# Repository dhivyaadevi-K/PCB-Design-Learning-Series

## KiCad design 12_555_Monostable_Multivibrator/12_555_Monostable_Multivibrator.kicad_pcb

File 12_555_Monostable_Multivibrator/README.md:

# 12 - NE555 Monostable Push-Button Timer

A beginner-friendly PCB project designed in KiCad 9 to practice building a 555 timer monostable ("one-shot") circuit, where pressing a push button lights an LED for a fixed duration.

Part of my **PCB Design Learning Series**, where I design and document circuits from basic to advanced using KiCad.

## Software Used

Designed in **KiCad 9**

## Overview

U1 (NE555P) is configured in monostable mode. Pressing SW1 momentarily pulls the TRIGGER pin (pin 2) low, starting a single timing cycle. During this cycle, the output (pin 3) goes high, lighting LED D1 through current-limiting resistor R3. After the timing period set by R2 and C1 elapses, the output returns low and the LED turns off — until the button is pressed again.

| J1 Pin | Signal | Description        |
|--------|--------|---------------------|
| 1      | +5V    | Power input          |
| 2      | GND    | Common ground        |

## How It Works

- R1 (10k) pulls the TRIGGER pin (pin 2) high when SW1 is not pressed, keeping the timer idle
- Pressing SW1 momentarily connects TRIGGER to GND, dropping it below 1/3 VCC and starting the timing cycle
- Once triggered, the output (pin 3, Q) goes high regardless of further trigger changes, lighting D1 through R3 (330 Ω)
- R2 (100k) and C1 (10 µF) set the output pulse duration, charging until the THRESHOLD pin (pin 6) reaches 2/3 VCC, at which point the output resets low and D1 turns off
- C2 (10n) on the CV pin (pin 5) stabilizes the internal reference voltage against noise
- Approximate pulse duration: **t ≈ 1.1 × R2 × C1**

## Features

- Through-hole PCB, beginner-friendly assembly
- Push-button triggered NE555 monostable (one-shot) timer
- LED lights for a fixed, predictable duration per button press
- Noise-stabilizing control voltage capacitor
- ERC and DRC verified
- Gerber and drill files included, ready for fabrication

## Components

| Component             | Qty |
|--------------------------|-----|
| NE555P Timer IC (U1)     | 1   |
| Push Button (SW1)        | 1   |
| LED (D1)                 | 1   |
| 330 Ω Resistor (R3)      | 1   |
| 10k Resistor (R1)        | 1   |
| 100k Resistor (R2)       | 1   |
| 10 µF Capacitor (C1)     | 1   |
| 10n Capacitor (C2)       | 1   |
| 2-Pin Header (J1)        | 1   |

## Repository Contents

- KiCad Schematic
- KiCad PCB
- Gerber Files
- Drill Files
- ERC Report
- DRC Report
- Images

## Images

### Schematic

### PCB Layout

### 3D View

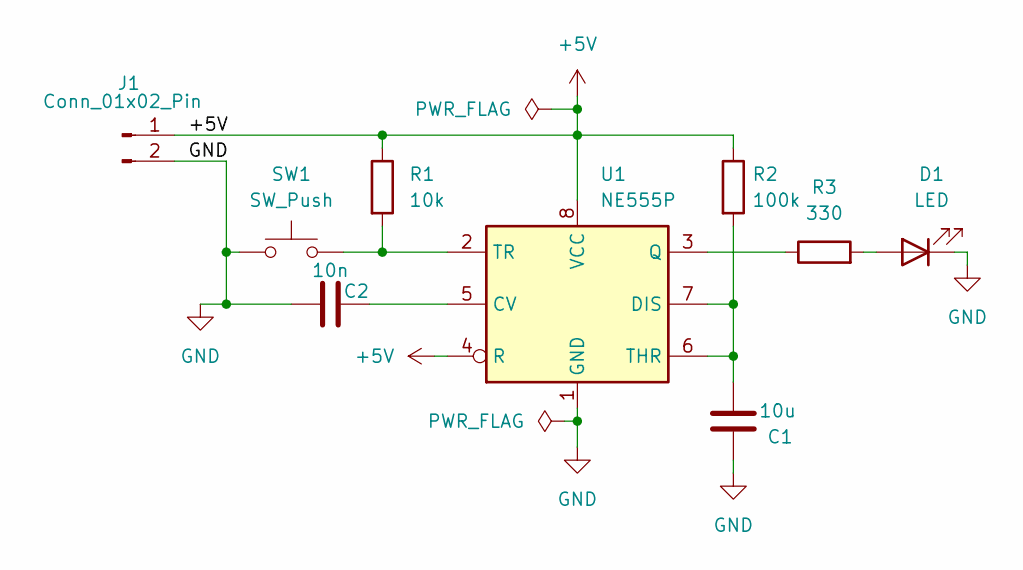
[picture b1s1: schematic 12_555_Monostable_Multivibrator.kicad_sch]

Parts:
C1: 10u; C_Disc_D5.0mm_W2.5mm_P5.00mm
C2: 10n; C_Disc_D5.0mm_W2.5mm_P5.00mm
D1: LED; LED_D5.0mm
J1: Conn_01x02_Pin; PinHeader_1x02_P2.54mm_Vertical
R1: 10k; R_Axial_DIN0207_L6.3mm_D2.5mm_P7.62mm_Horizontal
R2: 100k; R_Axial_DIN0207_L6.3mm_D2.5mm_P7.62mm_Horizontal
R3: 330; R_Axial_DIN0207_L6.3mm_D2.5mm_P7.62mm_Horizontal
SW1: SW_Push; SW_PUSH_6mm_H5mm
U1: NE555P; DIP-8_W7.62mm

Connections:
+5V: J1.1, R1.1, R2.1, U1.4 (R), U1.8 (VCC)
GND: C1.2, C2.1, D1.1 (K), J1.2, SW1.1, U1.1 (GND)
unnamed: D1.2 (A), R3.2
unnamed: C2.2, U1.5 (CV)
unnamed: C1.1, R2.2, U1.6 (THR), U1.7 (DIS)
unnamed: R3.1, U1.3 (Q)
unnamed: R1.2, SW1.2, U1.2 (TR)

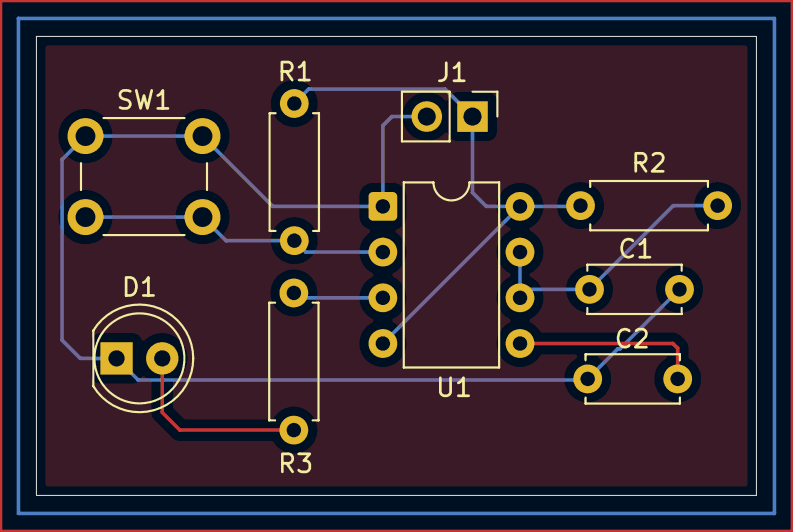
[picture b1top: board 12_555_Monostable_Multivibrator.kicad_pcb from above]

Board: 2 copper layers, 40.0 x 25.5 mm, 9 parts (0 on the bottom side), 7 nets.

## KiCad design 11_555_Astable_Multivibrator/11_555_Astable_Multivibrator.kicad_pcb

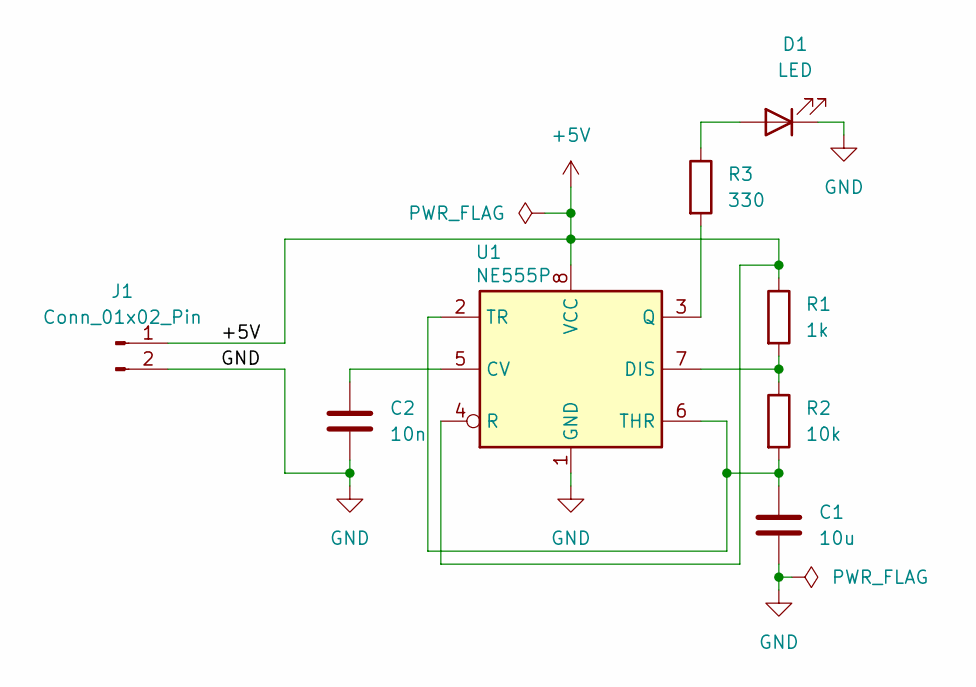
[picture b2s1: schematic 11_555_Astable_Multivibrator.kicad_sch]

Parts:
C1: 10u; C_Disc_D5.0mm_W2.5mm_P5.00mm
C2: 10n; C_Disc_D5.0mm_W2.5mm_P5.00mm
D1: LED; LED_D5.0mm
J1: Conn_01x02_Pin; PinHeader_1x02_P2.54mm_Vertical
R1: 1k; R_Axial_DIN0207_L6.3mm_D2.5mm_P7.62mm_Horizontal
R2: 10k; R_Axial_DIN0207_L6.3mm_D2.5mm_P7.62mm_Horizontal
R3: 330; R_Axial_DIN0207_L6.3mm_D2.5mm_P7.62mm_Horizontal
U1: NE555P; DIP-8_W7.62mm

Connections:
+5V: J1.1, R1.1, U1.4 (R), U1.8 (VCC)
GND: C1.2, C2.2, D1.1 (K), J1.2, U1.1 (GND)
unnamed: D1.2 (A), R3.1
unnamed: C2.1, U1.5 (CV)
unnamed: R1.2, R2.1, U1.7 (DIS)
unnamed: R3.2, U1.3 (Q)
unnamed: C1.1, R2.2, U1.2 (TR), U1.6 (THR)

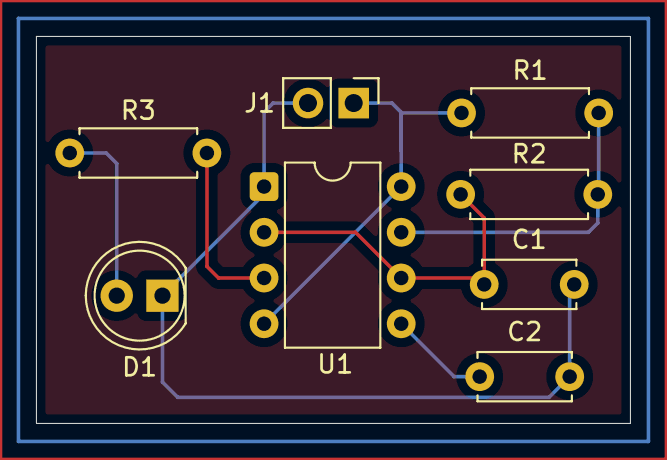
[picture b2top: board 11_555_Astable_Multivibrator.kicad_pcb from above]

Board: 2 copper layers, 33.0 x 21.5 mm, 8 parts (0 on the bottom side), 7 nets.

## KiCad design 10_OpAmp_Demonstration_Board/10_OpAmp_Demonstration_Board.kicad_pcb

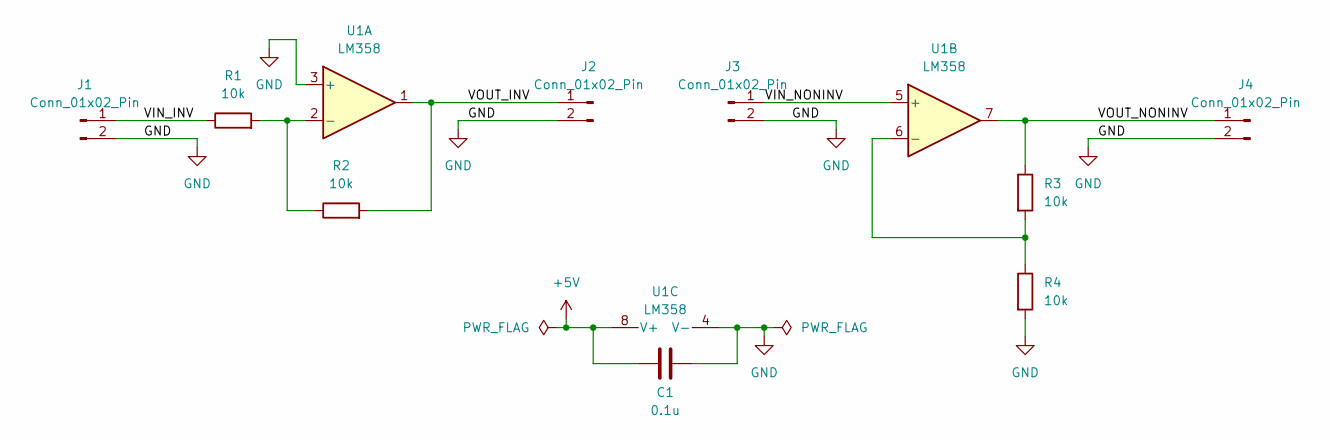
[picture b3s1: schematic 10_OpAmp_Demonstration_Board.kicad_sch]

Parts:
C1: 0.1u; C_Disc_D5.0mm_W2.5mm_P5.00mm
J1, J2, J3, J4: Conn_01x02_Pin; PinHeader_1x02_P2.54mm_Vertical
R1, R2, R3, R4: 10k; R_Axial_DIN0207_L6.3mm_D2.5mm_P7.62mm_Horizontal
U1: LM358; DIP-8_W7.62mm

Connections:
+5V: C1.1, U1.8 (V+)
/VIN_INV: J1.1, R1.1
/VIN_NONINV: J3.1, U1.5 (+)
/VOUT_INV: J2.1, R2.2, U1.1
/VOUT_NONINV: J4.1, R3.1, U1.7
GND: C1.2, J1.2, J2.2, J3.2, J4.2, R4.2, U1.3 (+), U1.4 (V-)
unnamed: R1.2, R2.1, U1.2 (-)
unnamed: R3.2, R4.1, U1.6 (-)

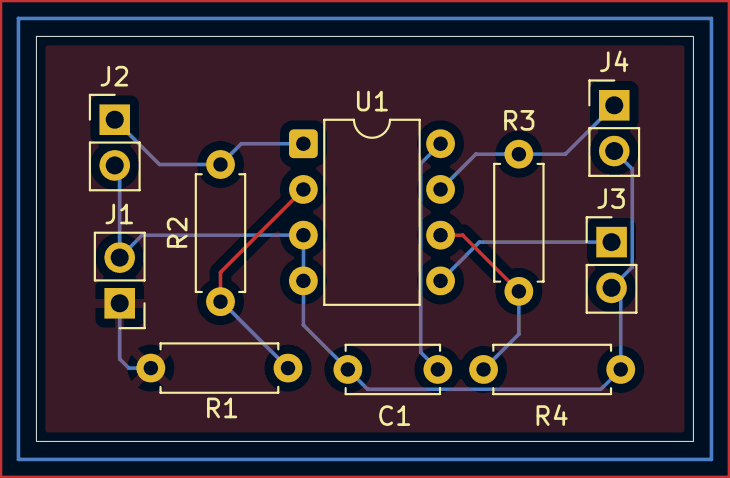
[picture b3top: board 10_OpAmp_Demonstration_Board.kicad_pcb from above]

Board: 2 copper layers, 36.5 x 22.5 mm, 10 parts (0 on the bottom side), 8 nets.

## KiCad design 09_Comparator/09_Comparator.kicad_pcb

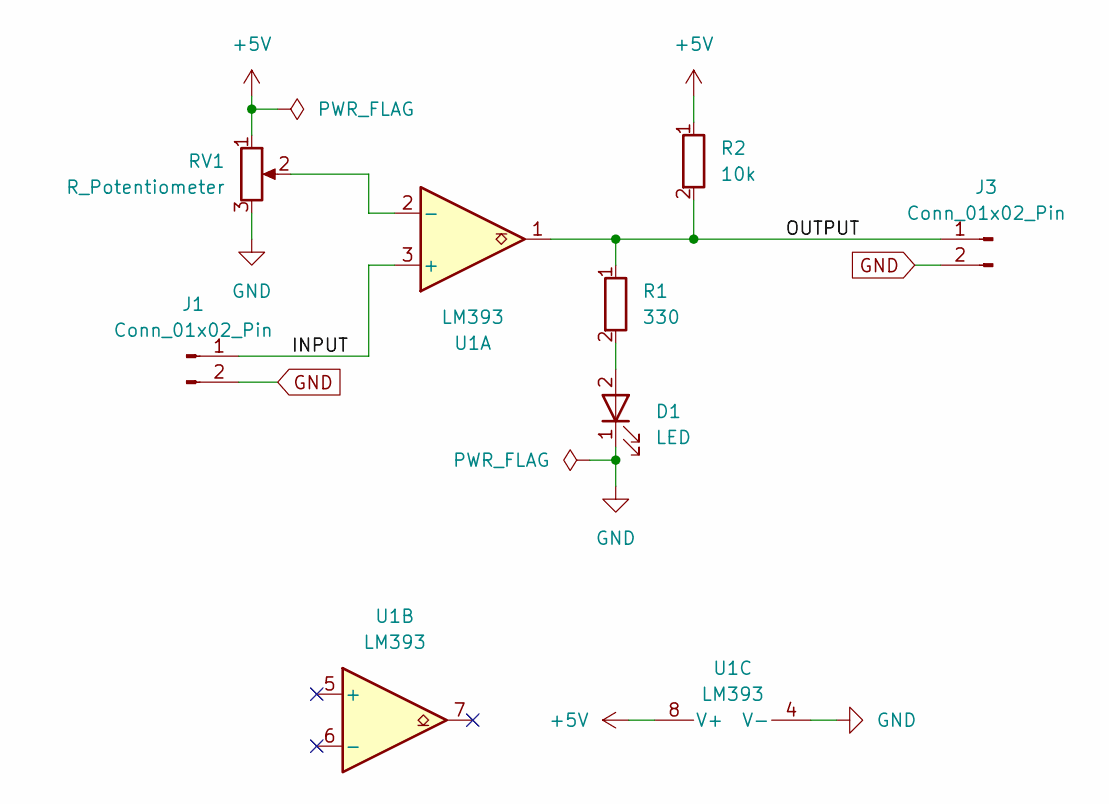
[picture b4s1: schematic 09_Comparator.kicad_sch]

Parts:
D1: LED; LED_D5.0mm
J1, J3: Conn_01x02_Pin; PinHeader_1x02_P2.54mm_Vertical
R1: 330; R_Axial_DIN0207_L6.3mm_D2.5mm_P7.62mm_Horizontal
R2: 10k; R_Axial_DIN0207_L6.3mm_D2.5mm_P7.62mm_Horizontal
RV1: R_Potentiometer; Potentiometer_Alps_RK09K_Single_Vertical
U1: LM393; DIP-8_W7.62mm_LongPads

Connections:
+5V: R2.1, RV1.1, U1.8 (V+)
/INPUT: J1.1, U1.3 (+)
/OUTPUT: J3.1, R1.1, R2.2, U1.1
GND: D1.1 (K), J1.2, J3.2, RV1.3, U1.4 (V-)
unnamed: D1.2 (A), R1.2
unnamed: RV1.2, U1.2 (-)

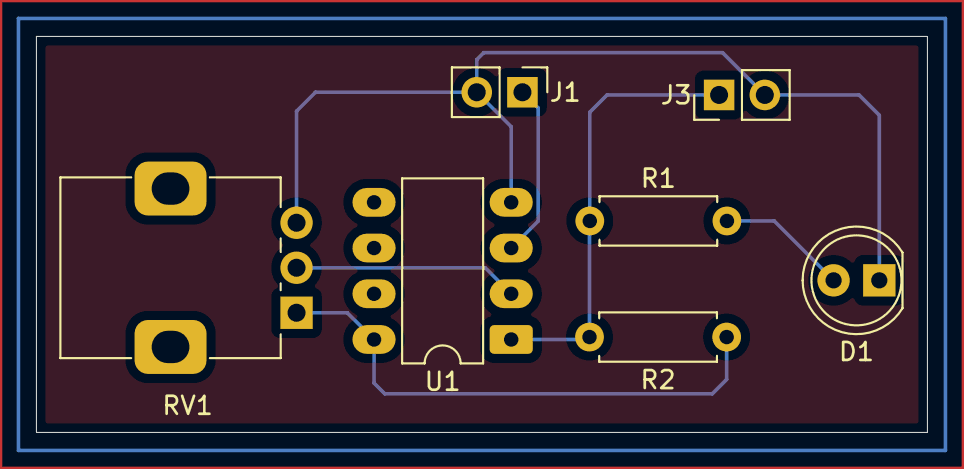
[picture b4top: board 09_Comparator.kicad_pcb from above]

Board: 2 copper layers, 49.5 x 22.0 mm, 7 parts (0 on the bottom side), 6 nets.

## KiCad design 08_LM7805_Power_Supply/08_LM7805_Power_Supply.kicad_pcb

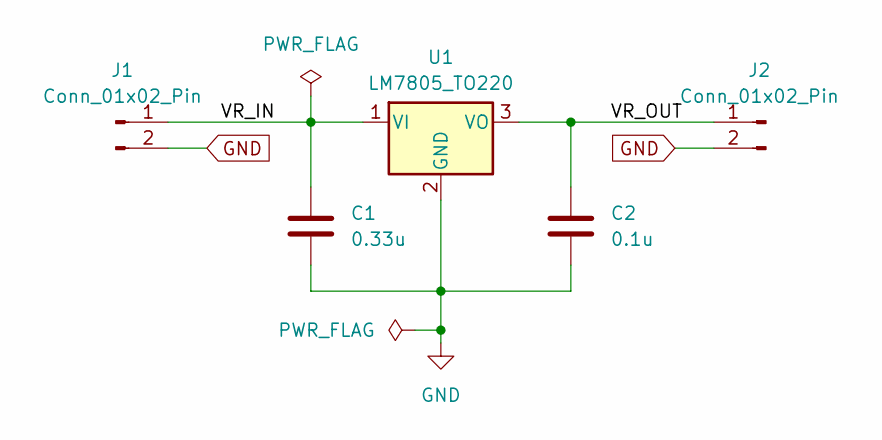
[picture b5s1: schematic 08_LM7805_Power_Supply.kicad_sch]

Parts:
C1: 0.33u; C_Disc_D5.0mm_W2.5mm_P5.00mm
C2: 0.1u; C_Disc_D5.0mm_W2.5mm_P5.00mm
J1, J2: Conn_01x02_Pin; PinHeader_1x02_P2.54mm_Vertical
U1: LM7805_TO220; TO-220-3_Vertical

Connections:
/VR_IN: C1.1, J1.1, U1.1 (VI)
/VR_OUT: C2.1, J2.1, U1.3 (VO)
GND: C1.2, C2.2, J1.2, J2.2, U1.2 (GND)

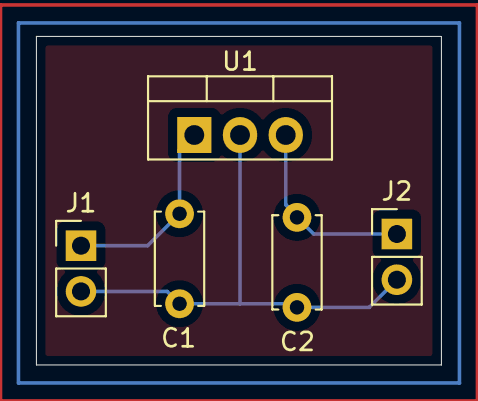
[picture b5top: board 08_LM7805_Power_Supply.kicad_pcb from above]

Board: 2 copper layers, 22.5 x 18.2 mm, 5 parts (0 on the bottom side), 3 nets.

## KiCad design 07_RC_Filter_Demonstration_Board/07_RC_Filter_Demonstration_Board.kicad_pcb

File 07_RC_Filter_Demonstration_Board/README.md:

# 07 - RC Filter Demonstration Board

A beginner-friendly PCB project designed in KiCad 9 to practice designing and understanding the four fundamental passive RC filter topologies: low-pass, high-pass, band-pass, and band-stop (notch).

Part of my **PCB Design Learning Series**, where I design and document circuits from basic to advanced using KiCad.

## Software Update

Designed in **KiCad 9**

## Overview

This board combines four independent RC filter circuits on a single PCB, each with its own input/output header, so each filter's behavior can be tested and compared individually.

| Filter          | Input Header | Output Header | Components         |
|------------------|--------------|-----------------|----------------------|
| Low Pass         | J1 (LP_IN)   | J2 (LP_OUT)     | R1 (1k), C1 (100n)  |
| High Pass        | J3 (HP_IN)   | J4 (HP_OUT)     | C2 (100n), R2 (1k)  |
| Band Pass        | J5 (BP_IN)   | J6 (BP_OUT)     | C3 (100n), R4 (1k), R3 (1k), C4 (100n) |
| Band Stop (Notch)| J7 (BS_IN)   | J8 (BS_OUT)     | R5 (1k), R6 (1k), C7 (200n), C5 (100n), C6 (100n), R7 (500) |

## How It Works

- **Low Pass**: R1 and C1 form a simple RC low-pass filter — allows low frequencies through while attenuating high frequencies above the cutoff
- **High Pass**: C2 and R2 form the inverse — attenuates low frequencies, passes high frequencies above the cutoff
- **Band Pass**: combines high-pass and low-pass stages (C3/R3 and R4/C4) to pass only a middle band of frequencies
- **Band Stop (Notch)**: a twin-T style network (R5/R6/C7/C5/C6/R7) that attenuates a specific frequency band while passing frequencies above and below it

Each filter section is fully independent — separate input/output headers mean any one filter can be tested in isolation with a function generator and oscilloscope.

## Features

- Through-hole PCB, beginner-friendly assembly
- 4 independent passive RC filter topologies on one board
- Separate I/O headers per filter for isolated testing
- ERC and DRC verified
- Gerber and drill files included, ready for fabrication

## Components

| Component        | Qty |
|-------------------|-----|
| Resistors (1k)     | 5   |
| Resistor (500 Ω)   | 1   |
| Capacitors (100n)  | 4   |
| Capacitor (200n)   | 1   |
| 2-Pin Headers (J1–J8) | 8 |

## Repository Contents

- KiCad Schematic
- KiCad PCB
- Gerber Files
- Drill Files
- ERC Report
- DRC Report
- Images

## Images

### Schematic

### PCB Layout

### 3D View

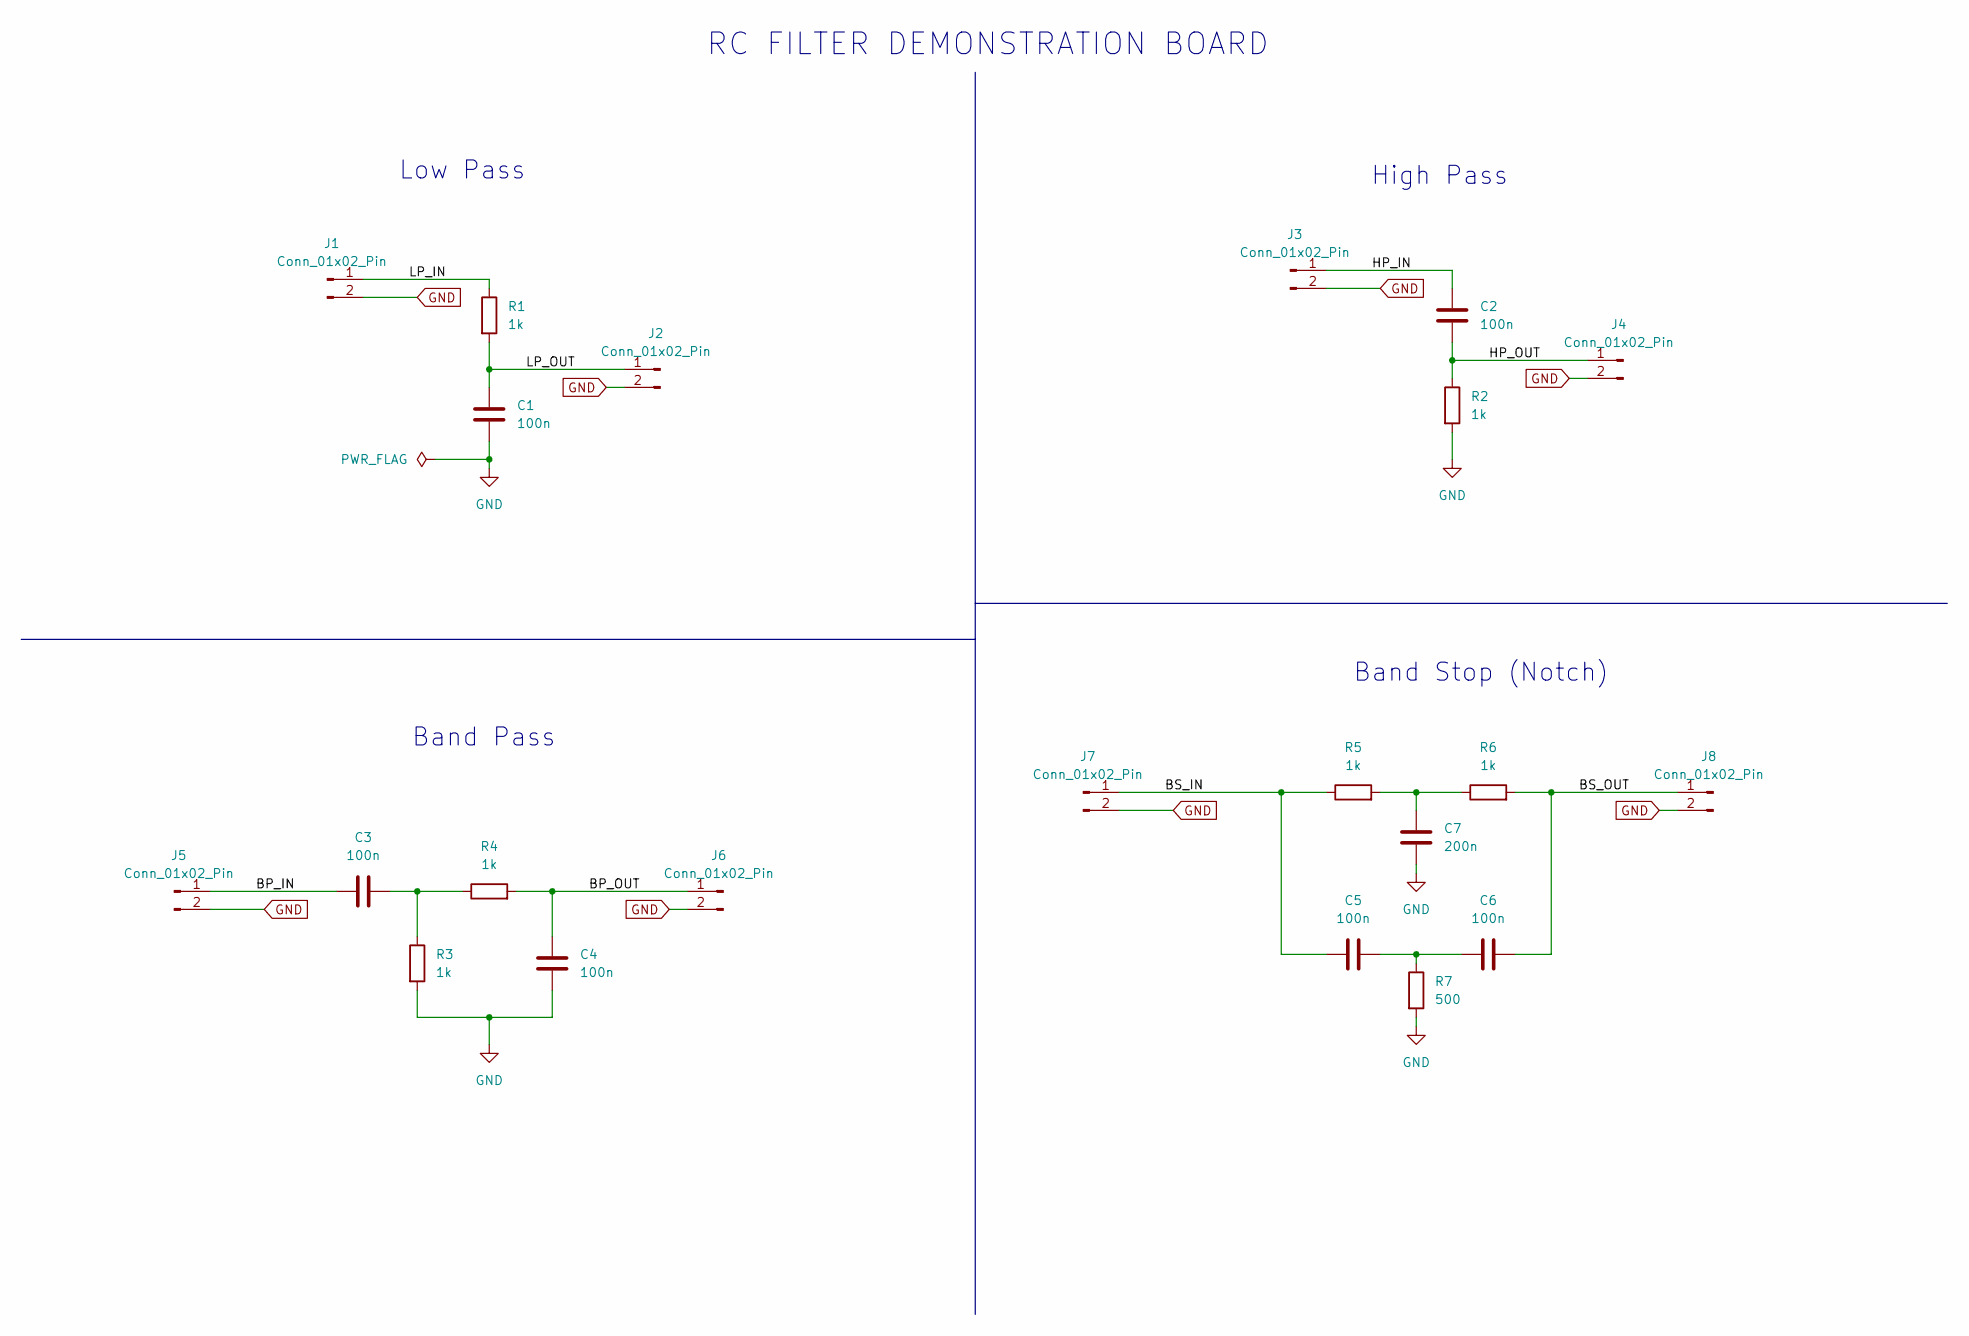
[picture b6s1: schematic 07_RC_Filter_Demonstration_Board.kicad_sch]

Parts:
C1, C2, C3, C4, C5, C6: 100n; C_Disc_D5.0mm_W2.5mm_P5.00mm
C7: 200n; C_Disc_D5.0mm_W2.5mm_P5.00mm
J1, J2, J3, J4, J5, J6, J7, J8: Conn_01x02_Pin; PinHeader_1x02_P2.54mm_Vertical
R1, R2, R3, R4, R5, R6: 1k; R_Axial_DIN0207_L6.3mm_D2.5mm_P7.62mm_Horizontal
R7: 500; R_Axial_DIN0207_L6.3mm_D2.5mm_P7.62mm_Horizontal

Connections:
/BP_IN: C3.1, J5.1
/BP_OUT: C4.1, J6.1, R4.2
/BS_IN: C5.1, J7.1, R5.1
/BS_OUT: C6.2, J8.1, R6.2
/HP_IN: C2.1, J3.1
/HP_OUT: C2.2, J4.1, R2.1
/LP_IN: J1.1, R1.1
/LP_OUT: C1.1, J2.1, R1.2
GND: C1.2, C4.2, C7.2, J1.2, J2.2, J3.2, J4.2, J5.2, J6.2, J7.2, J8.2, R2.2, R3.2, R7.2
unnamed: C3.2, R3.1, R4.1
unnamed: C5.2, C6.1, R7.1
unnamed: C7.1, R5.2, R6.1

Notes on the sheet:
Band Stop (Notch)
High Pass
Low Pass
RC FILTER DEMONSTRATION BOARD
Band Pass

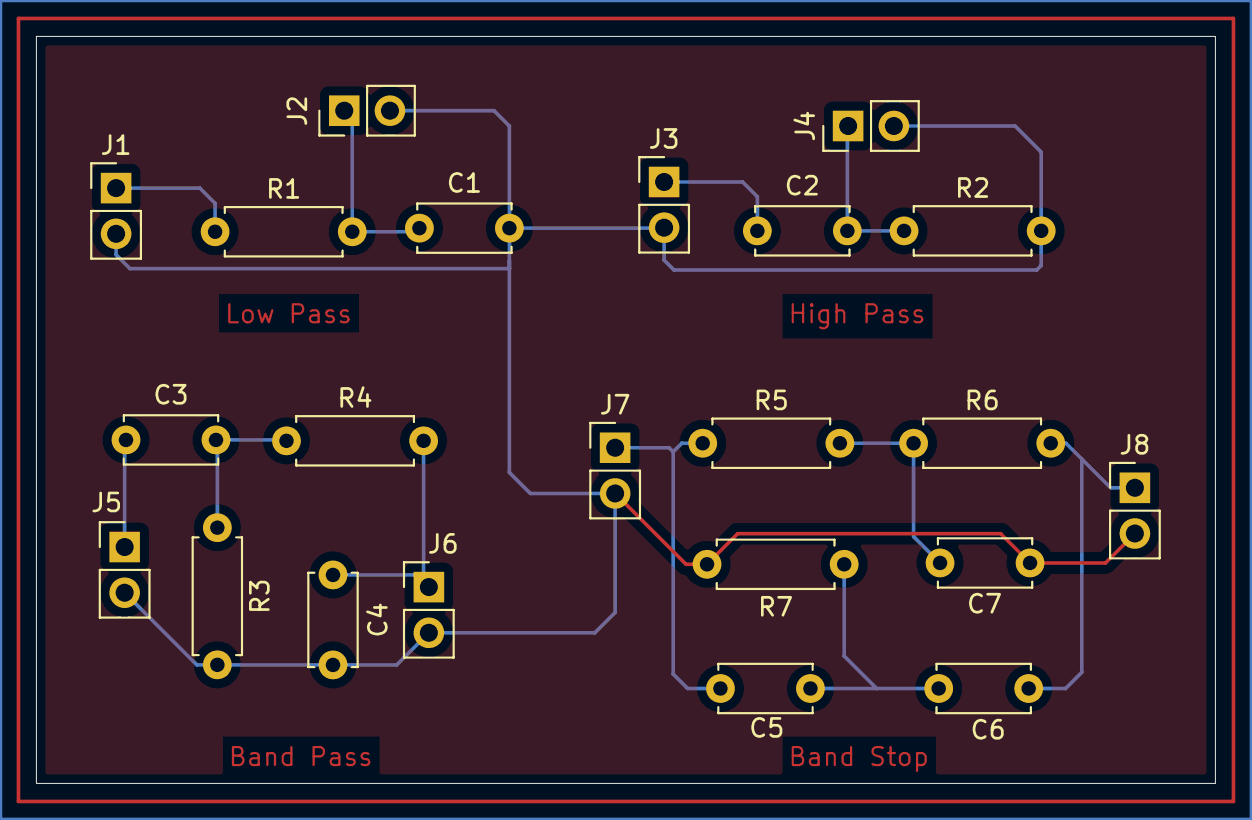
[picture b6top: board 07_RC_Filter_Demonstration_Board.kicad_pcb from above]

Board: 2 copper layers, 65.5 x 41.5 mm, 22 parts (0 on the bottom side), 12 nets.

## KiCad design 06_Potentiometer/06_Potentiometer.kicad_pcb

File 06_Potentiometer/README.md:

# 06 - Potentiometer LED Dimmer

A beginner-friendly PCB project designed in KiCad 9 to practice manual brightness control of an LED using a potentiometer as a variable voltage divider.

Part of my **PCB Design Learning Series**, where I design and document circuits from basic to advanced using KiCad.

## Software Used

Designed in **KiCad 9**

## Overview

R1 (220 Ω) and RV1 (potentiometer) form an adjustable voltage divider feeding the LED (D1). Turning the potentiometer's wiper changes the voltage delivered to the LED, allowing manual brightness adjustment from off to full brightness.

| J1 Pin | Signal | Description        |
|--------|--------|---------------------|
| 1      | +5V    | Power input          |
| 2      | GND    | Common ground        |

## How It Works

- +5V feeds through R1 into RV1 (potentiometer), which acts as a variable resistor
- The potentiometer's wiper (terminal 2) taps off a variable voltage, which drives the LED
- Turning the pot's wiper toward one end increases voltage to the LED (brighter); toward the other end decreases it (dimmer)
- R1 (220 Ω) protects the LED from excess current even when the potentiometer is at its lowest resistance setting

## Features

- Through-hole PCB, beginner-friendly assembly
- Manual LED brightness control via potentiometer
- Current-limiting resistor to protect the LED at all pot settings
- ERC and DRC verified
- Gerber and drill files included, ready for fabrication

## Components

| Component               | Qty |
|--------------------------|-----|
| Potentiometer (RV1)      | 1   |
| LED (D1)                 | 1   |
| 220 Ω Resistor (R1)      | 1   |
| 2-Pin Header (J1)        | 1   |

## Repository Contents

- KiCad Schematic
- KiCad PCB
- Gerber Files
- Drill Files
- ERC Report
- DRC Report
- Images

## Images

### Schematic

### PCB Layout

### 3D View

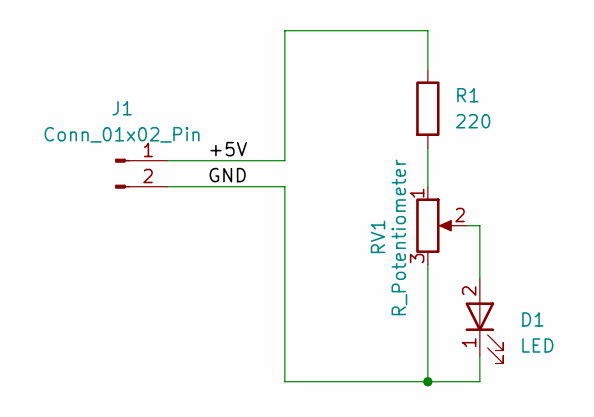
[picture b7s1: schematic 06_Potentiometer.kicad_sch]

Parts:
D1: LED; LED_D5.0mm
J1: Conn_01x02_Pin; PinHeader_1x02_P2.54mm_Vertical
R1: 220; R_Axial_DIN0207_L6.3mm_D2.5mm_P7.62mm_Horizontal
RV1: R_Potentiometer; Potentiometer_Alps_RK09K_Single_Vertical

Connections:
/+5V: J1.1, R1.1
/GND: D1.1 (K), J1.2, RV1.3
unnamed: D1.2 (A), RV1.2
unnamed: R1.2, RV1.1

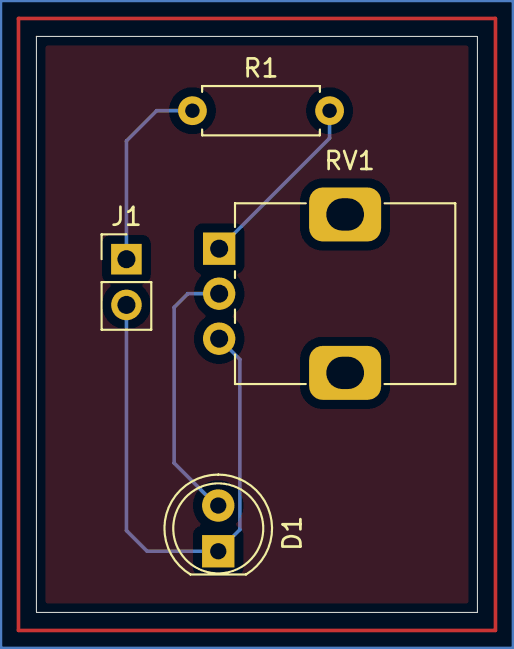
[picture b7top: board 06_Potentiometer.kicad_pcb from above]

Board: 2 copper layers, 24.5 x 32.0 mm, 4 parts (0 on the bottom side), 4 nets.

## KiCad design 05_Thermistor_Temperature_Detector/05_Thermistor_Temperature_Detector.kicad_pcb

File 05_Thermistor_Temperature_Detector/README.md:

# 05 - Thermistor-Based Temperature Indicator Circuit

A beginner-friendly PCB project designed in KiCad 9 to practice building a temperature-sensing circuit using a thermistor in a voltage divider, driving an LED through a transistor switch.

Part of my **PCB Design Learning Series**, where I design and document circuits from basic to advanced using KiCad.

## Software Used

Designed in **KiCad 9**

## Overview

R1 (10k) and TH1 (thermistor) form a voltage divider. As temperature changes, the thermistor's resistance changes, shifting the voltage at the divider's midpoint feeding Q1's base. This turns Q1 on or off, switching the LED (D1) accordingly.

| J1 Pin | Signal | Description        |
|--------|--------|---------------------|
| 1      | GND    | Common ground        |
| 2      | +5V    | Power input          |

## How It Works

- Thermistors are temperature-dependent resistors — most common types (NTC) decrease in resistance as temperature rises
- As temperature changes, the divider midpoint voltage shifts, turning Q1 on or off
- R3 (330 Ω) limits current through the LED
- This circuit demonstrates the same voltage-divider + transistor-switch principle as the LDR project, but using a thermistor instead — useful for basic over-temperature indicators

## Features

- Through-hole PCB, beginner-friendly assembly
- Thermistor-based voltage divider for temperature sensing
- NPN transistor (BC547) as a switch
- Visual LED indicator triggered by temperature change
- ERC and DRC verified
- Gerber and drill files included, ready for fabrication

## Components

| Component             | Qty |
|-------------------------|-----|
| Thermistor (TH1)         | 1   |
| NPN Transistor (Q1)      | 1   |
| LED (D1)                 | 1   |
| 330 Ω Resistor (R3)      | 1   |
| 10k Resistor (R1)        | 1   |
| 2-Pin Socket (J1)        | 1   |

## Repository Contents

- KiCad Schematic
- KiCad PCB
- Gerber Files
- Drill Files
- ERC Report
- DRC Report
- Images

## Images

### Schematic

### PCB Layout

### 3D View

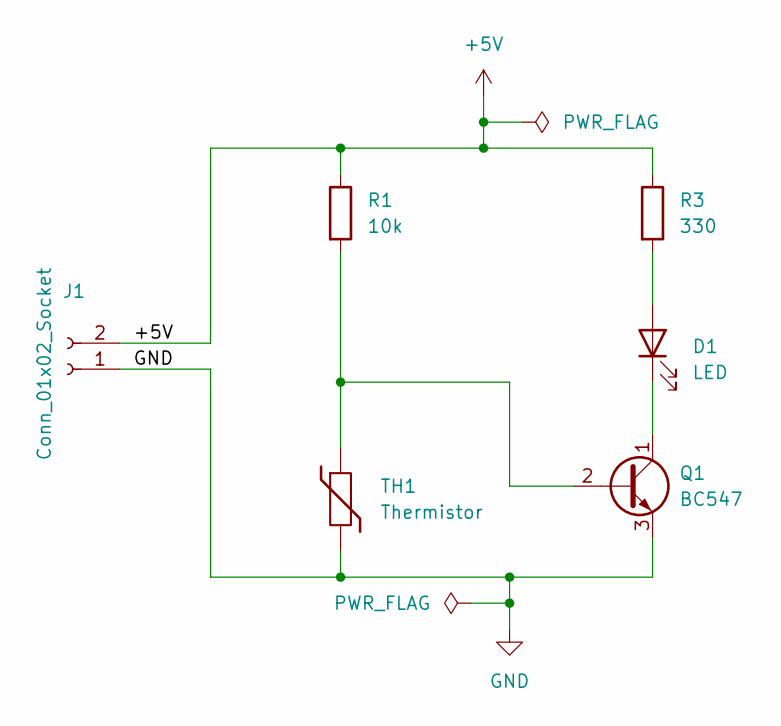
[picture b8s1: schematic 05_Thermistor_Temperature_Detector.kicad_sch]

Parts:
D1: LED; LED_D5.0mm
J1: Conn_01x02_Socket; PinSocket_1x02_P2.54mm_Vertical
Q1: BC547; TO-92_Inline
R1: 10k; R_Axial_DIN0207_L6.3mm_D2.5mm_P7.62mm_Horizontal
R3: 330; R_Axial_DIN0207_L6.3mm_D2.5mm_P7.62mm_Horizontal
TH1: Thermistor

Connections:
+5V: J1.2, R1.1, R3.1
GND: J1.1, Q1.3 (E), TH1.2
unnamed: D1.2 (A), R3.2
unnamed: D1.1 (K), Q1.1 (C)
unnamed: Q1.2 (B), R1.2, TH1.1

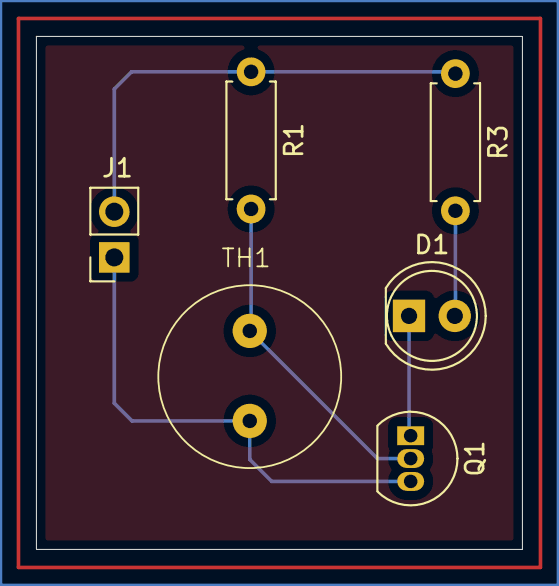
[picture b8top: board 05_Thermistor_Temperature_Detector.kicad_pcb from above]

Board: 2 copper layers, 27.0 x 28.5 mm, 6 parts (0 on the bottom side), 5 nets.
